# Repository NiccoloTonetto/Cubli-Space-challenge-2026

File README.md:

# Cubli — Space Challenge 2026

A 156 mm reaction-wheel cube that balances on an **edge** and on a **corner**,
taken from Lagrangian derivation through Simscape multibody simulation to
working hardware — and validated against its own flight telemetry.

*Standing on a single corner, unsupported. Three reaction wheels, a Teensy 4.1
closing a 400 Hz loop, and a gain set designed for this specific corner.*

And the telemetry underneath it — six minutes of exactly that, without falling:

*373 s continuous. Tilt RMS 0.40°, peak 1.25°, wheels never reaching the
40 rad/s policy cap. Raw log:
[`data/corner/corner-balance-373s-2026-08-20.log`](data/corner/corner-balance-373s-2026-08-20.log).*

---

## What it achieves

| | Result | Source |
|---|---|---|
| **Corner balance, longest run** | **373.5 s continuous**, tilt RMS **0.40°**, max 1.25° | [log](data/corner/corner-balance-373s-2026-08-20.log) |
| **Corner balance, quietest run** | 278 s, tilt RMS **0.25°**, max 0.92° | [log](data/corner/FINAL_CALIBRATION.log) |
| **Edge balance** | **197 s continuous**, tilt RMS 0.58° | [log](data/edge/1minEDGE.log) · [report](docs/testing/Corner-RateFilter-and-Edge-Hardware-Tests-2026-08-19.md#4-edge--1-min-quiet-hold) |
| **Disturbance rejection** | recovers ~3° pushes in **0.08–0.20 s**; trips at the 25° policy limit | [report §3](docs/testing/Corner-RateFilter-and-Edge-Hardware-Tests-2026-08-19.md#3-pushes--how-hard-until-it-falls) |
| **Edge release** | recovers from **6.18°**, settles under 0.5° by 9.6 s | [report §5](docs/testing/Corner-RateFilter-and-Edge-Hardware-Tests-2026-08-19.md#5-edge--recovery-from-6) |
| **Predicted envelope** | 2.76°–3.14° worst-case recovery, all 8 corners | [envelope study](docs/dynamics/Cube-Performance-Envelope-Results.md#per-corner-results-own-gains-supersedes-part-2-3s-table) |

The hardware sits inside the envelope the simulation predicted, and the run above
is *momentum*-bound rather than torque-bound — exactly the binding constraint the
model identified before the cube was ever switched on.

## The system

| | |
|---|---|
| **Structure** | 156 mm printed PETG-CF frame, 1.615 kg assembled, 3 ballasted reaction wheels |
| **Actuation** | 3 × T-Motor Antigravity 4006 (Kt 0.02513 N·m/A) on 3 × [mjbots moteus-n1](https://mjbots.com) FOC drivers, 5 Mbps CAN-FD |
| **Sensing** | Bosch BMI270 IMU at the cube's geometric centre — 130 mm from *every* corner |
| **Compute** | Teensy 4.1 running the 400 Hz control loop; XIAO ESP32-C6 as a Wi-Fi telemetry bridge |
| **Estimator** | reduced-attitude complementary filter with gyro-bias states (`kP = 4`, `kI = 0.5`) |
| **Control** | per-corner and per-edge reduced-order LQR, yaw-projected — 8 corner gain sets, 12 edge gain sets |
| **Operating point** | τ_max 0.12 N·m, wheel-speed cap 40 rad/s (firmware policy, not a hardware limit) |

## The engineering story

**1 — Derive the plant.** The [3D Lagrangian derivation](docs/dynamics/3D-Cubli-Lagrangian-Derivation.md)
is worked from scratch and specialised to the 1D/2D edge case, with
[CAD → model parameters](docs/dynamics/Deriving-Dynamics-from-CAD.md) and an
[attitude-representation study](docs/dynamics/Quaternions-Complete-Guide.md)
that ends up rejecting quaternions for corner balance and choosing a reduced
attitude instead — [argued, not assumed](docs/dynamics/Attitude-Representation-for-Firmware.md).

**2 — Prove it on a 2D panel first.** A [Simscape panel model](docs/simulation/Simscape-Panel-Model-Build-Guide.md)
with four dedicated nonlinearity studies — [saturation envelope](docs/simulation/reports/Saturation-Envelope-Test-Block-A.md),
[discrete-loop delay](docs/simulation/reports/Discrete-Loop-Test-Block-B.md),
[IMU lever arm](docs/simulation/reports/IMU-Lever-Arm-Estimator-Block-C.md),
[friction sensitivity](docs/simulation/reports/Friction-Sensitivity-Block-D.md).
The [1D-jig-to-3D-cube strategy](docs/dynamics/1D-Jig-to-3D-Cube-Strategy.md)
states exactly what transfers and what does not.

**3 — Build the cube model three ways.** A 9-state linear design plant, a
Simscape multibody model built from imported STEP geometry, and a fast nonlinear
plant with sensors and actuator limits. They agree to
[`A err 1.7e-07`](docs/dynamics/Cube-Performance-Envelope-Results.md#validation-chain)
and within 1 % through the transient — which is what makes the thousands of
bisection runs behind the recovery envelope trustworthy.

<table>
<tr>
<td width="50%"></td>
<td width="50%"></td>
</tr>
<tr>
<td><b>The accelerometer lever arm is the dominant sensing effect.</b> Fed raw, the
cube falls every time, at any IMU position. The complementary filter rejects it
almost entirely — but there is a cliff past ~150 mm, which is why the IMU sits at
the geometric centre.</td>
<td><b>All eight corners balance, but each needs its own gains.</b> Apply the
primary corner's gains elsewhere and six corners diverge at the open-loop rate.
The antipodal corner <i>almost</i> works — a 13 s fall that short tests score as
a pass.</td>
</tr>
</table>

**4 — Find the real limits, then design to them.** A 48-point Bryson grid moves
the envelope by 2 %; the [actuator chart](figures/simulation/png/actuator_chart.png)
moves it by 4×. The conclusion — *the envelope is set by hardware, not by the
controller* — is what makes the rest of the project honest about what tuning can
and cannot buy. The shipped weights are chosen on
[robustness to inertia error](figures/simulation/png/qw_robustness.png), not on
peak performance: `qw = 10` costs 4 % against the grid optimum and is the only
set that survives ±20 % on Θ.

**5 — Climb a staged bring-up ladder on hardware.** Every control mode is reached
through the same five stages, each of which must pass before the next is flashed:
open-loop torque → damping only → position + damping → full law → release. The
ladders live in [`firmware/`](firmware/) — [panel](firmware/panel-bringup/),
[cube](firmware/cube-bringup/), [edge](firmware/edge-bringup/),
[corner](firmware/corner-bringup/), and a separate [Wi-Fi link ladder](firmware/link-bringup/).

**6 — Measure, and correct the record when it disagrees.** The
[hardware test reports](docs/testing/) are written to be falsifiable: the
rate-filter A/B is reported as **not a clean comparison** and the reasons are
given; a firmware comment claiming "20–30 dB of attenuation" is shown to be
**~6 dB** with the filter theory to prove a first-order filter cannot do better.
Simulation values that later proved wrong are struck through and corrected in
place rather than quietly edited.

## Repository map

```
├── docs/           theory, design studies and test reports
│   ├── dynamics/       Lagrangian derivation, attitude, CAD→parameters, cube envelope
│   ├── simulation/     panel model build guide + 4 nonlinearity studies + cube envelope
│   ├── testing/        hardware test campaigns, fine-tuning plan
│   ├── electronics/    electrical design guide + schematic PDFs
│   ├── bom/            component reference, motor notes, CAD↔BOM handoff
│   └── references/     literature, with DOIs
├── simulation/     MATLAB + Simulink/Simscape
│   ├── panel-2d/       the 1D/2D panel model and its LQR design
│   ├── cube-3d/        the 3D cube: params, plant, nonlinear sim, Simscape, studies, CAD
│   └── validation/     tools that plot hardware telemetry against the model
├── firmware/       Teensy + XIAO, organised as bring-up ladders
│   ├── panel-bringup/  cube-bringup/  edge-bringup/  corner-bringup/  link-bringup/
│   ├── cubli-ui/       the consolidated final system: firmware, dashboard, tools
│   ├── imu-calibration/  xiao/
│   └── archive/        superseded builds, kept for provenance
├── data/           curated flight telemetry (see data/README.md for formats)
├── figures/        every plot, render and demo video
└── hardware/       KiCad schematic, PCB and project libraries
```

## Reproducing the results

**Simulation** needs MATLAB with Simulink, Simscape and Simscape Multibody, plus
the Control System Toolbox. See [`simulation/README.md`](simulation/README.md)
for the exact run order — several scripts depend on workspace state left by
earlier ones and will tell you so if you skip ahead.

```matlab
addpath(genpath('simulation'))
cubli_demo          % self-contained 3D recovery demo — no Simulink needed
```

**Firmware** is Arduino-IDE / `arduino-cli` sketches for Teensy 4.1 and XIAO
ESP32-C6. Start at [`firmware/README.md`](firmware/README.md); to actually run
the cube, [`firmware/cubli-ui/README.md`](firmware/cubli-ui/README.md) is
self-contained.

## Who did what

This was a two-person build for the Space Challenge Sofia 2026 programme, and the
repository contains both people's work.

**Niccolò Tonetto** — dynamics and all written analysis ([`docs/`](docs/) is
entirely mine): the Lagrangian derivation, attitude-representation study,
CAD-to-parameters method, the 2D panel Simscape model and its four nonlinearity
studies, the 3D cube simulation chain (per-corner plant, reduced-order LQR,
nonlinear sim, recovery-envelope sweeps, figure generation), the electronics —
[schematic, PCB and BOM](hardware/) — and the five-stage bring-up ladder used for
every control mode.

**Pablo Urioste** ([@pablourioste](https://github.com/pablourioste)) — the
telemetry and Wi-Fi stack and the tooling around it: the XIAO bridge, the
[`cubli-ui`](firmware/cubli-ui/) dashboard and analysis tools, the Wi-Fi variants
of the bring-up stages, and IMU calibration.

The `git log` is the authoritative record; `git shortlog -sn` gives the split.

## Status and honest limits

This is a working balance controller, not a finished vehicle. Known gaps, all
documented rather than hidden:

- **Only corner `[-1,-1,-1]` has been flown.** All eight corners are
  geometry-complete and have verified gain designs, but the `Kp` matrices for
  corners 2–8 have not been transcribed into firmware — and running a corner on
  the wrong corner's gains is [worse than not identifying it at all](docs/dynamics/Cube-Performance-Envelope-Results.md#whats-not-re-derived-yet).
- **Multi-corner locomotion is currently off the table on six of eight corners.**
  A structural strut added during bring-up shifted the COM enough that their
  equilibrium tilt now exceeds their own recovery envelope. The analysis is
  [in the repo](docs/dynamics/Cube-Performance-Envelope-Results.md#multi-corner-picture--the-finding-that-matters); the fix is a counterweight, not a gain change.
- **No jump-up.** Balance only — the braking jump-up of the ETH papers was not attempted.
- **Edge balance has no simulation study.** It went straight from estimator design
  to staged hardware bring-up, so its numbers are measured, not predicted, and the
  reports say so.
- **Several plant parameters are still estimates** — wheel Coulomb friction, viscous
  damping and the real continuous-torque limit are flagged `PLACEHOLDER` in
  [`cubli_gains.h`](firmware/cubli-ui/teensy/cubli_gains.h) pending spin-down and
  thermal tests.
- **The wheel-speed cap costs about 20 % of available capability.** Raising it
  requires balanced wheels and a re-run of the gain grid, in that order — it is
  not a constant you can edit.

## References

Full citations with DOIs in [`docs/references/`](docs/references/README.md). The
core prior art is the ETH Zurich Cubli — Gajamohan et al. (IROS 2012, ECC 2013)
and Muehlebach & D'Andrea (IEEE TCST 2017).

## License

Original work in this repository is MIT licensed — see [LICENSE](LICENSE).
Third-party vendor libraries, JavaScript and fonts keep their own licenses —
see [NOTICE](NOTICE).

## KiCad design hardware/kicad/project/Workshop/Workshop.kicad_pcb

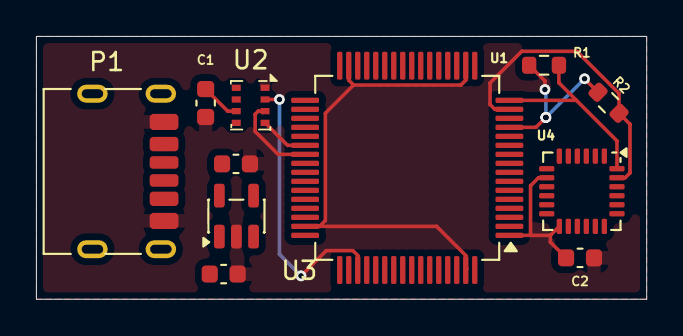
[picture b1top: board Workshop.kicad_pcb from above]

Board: 2 copper layers, 33.9 x 14.6 mm, 11 parts (0 on the bottom side), 10 nets.

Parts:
C1, C2: 100nF; C_0603_1608Metric
Cin1: 1uF; C_0603_1608Metric
Cout1: 1uF; C_0603_1608Metric
P1: USB_C_Plug_USB2.0; USB_C_Receptacle_HRO_TYPE-C-31-M-17
R1, R2: 4.7k; R_0603_1608Metric
U1: STM32F446RETx; LQFP-64_10x10mm_P0.5mm
U2: BMP280; Bosch_LGA-8_2x2.5mm_P0.65mm_ClockwisePinNumbering
U3: MCP1804x-3302xOT; SOT-23-5
U4: MPU-6050; InvenSense_QFN-24_4x4mm_P0.5mm

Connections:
+3.3V: C1.1, C2.1, Cout1.1, R1.1, R2.1, U1.1 (VBAT), U1.13 (VDDA), U2.6 (VDDIO), U2.8 (VDD), U3.5 (VOUT), U4.8 (VLOGIC), U4.13 (VDD)
+5V: Cin1.1, P1.A9 (VBUS), P1.B9 (VBUS), U3.1 (VIN), U3.4 (~SHDN)
/CSB: U1.51 (PC10), U2.2 (CSB)
/IMU_SCL: R2.2, U1.15 (PA1), U4.23 (SCL)
/IMU_SDA: R1.2, U1.16 (PA2), U4.24 (SDA)
/SCK: U1.38 (PC7), U2.4 (SCK)
/SDI: U1.39 (PC8), U2.3 (SDI)
/SDO: U1.40 (PC9), U2.5 (SDO)
GND: C1.2, C2.2, Cin1.2, Cout1.2, P1.A12 (GND), P1.B12 (GND), U2.1 (GND), U2.7 (GND), U3.2 (GND), U4.18 (GND)
unnamed: U1.18 (VSS), U1.31 (VSS), U1.47 (VSS), U1.63 (VSS)
